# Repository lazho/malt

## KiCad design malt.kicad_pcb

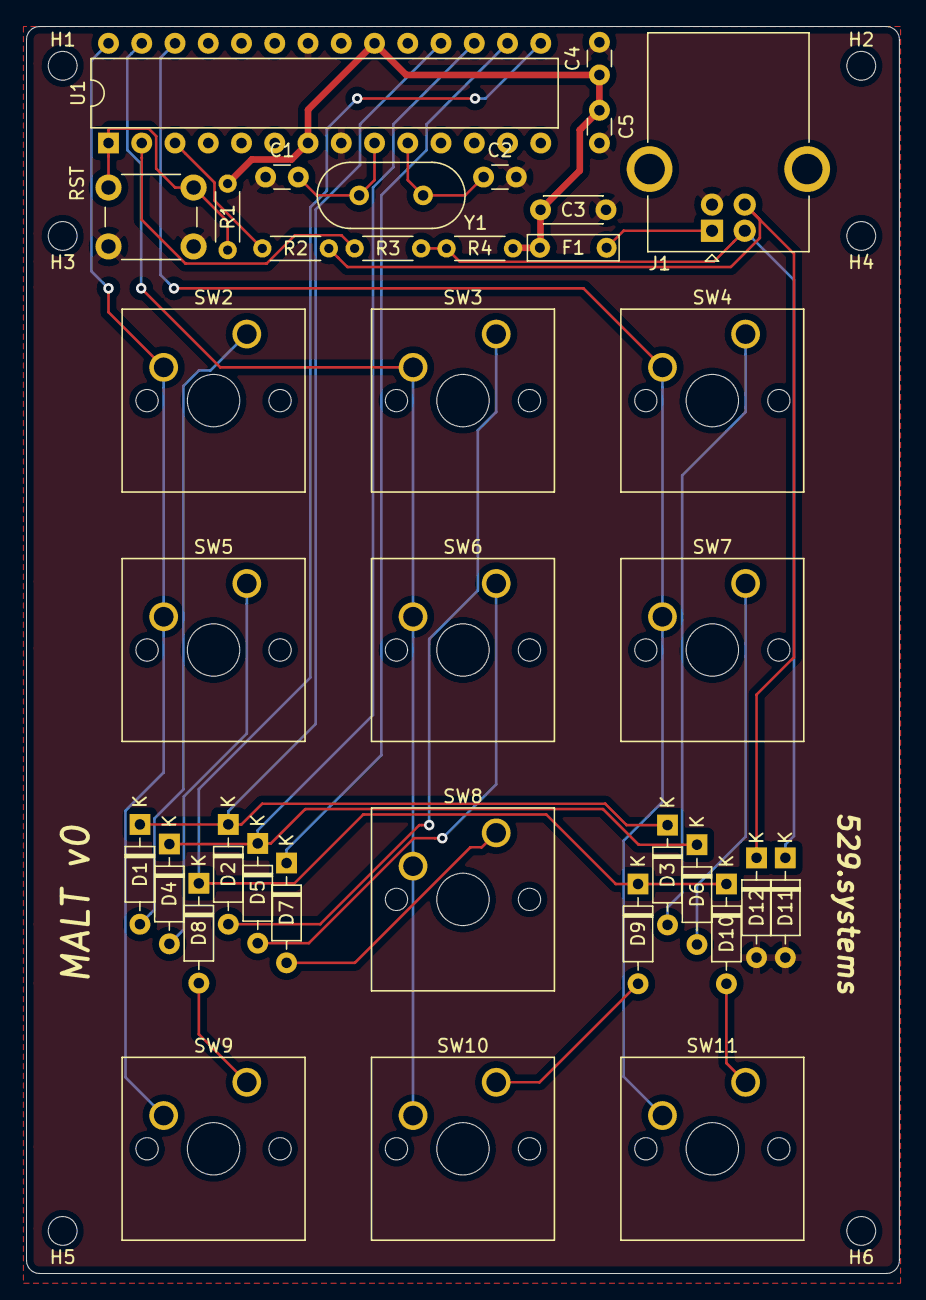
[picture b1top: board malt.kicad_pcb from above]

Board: 2 copper layers, 66.7 x 95.2 mm, 42 parts (0 on the bottom side), 27 nets.

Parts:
C1, C2: 20p; C_Disc_D3.0mm_W1.6mm_P2.50mm
C3: 4.7u; C_Disc_D4.3mm_W1.9mm_P5.00mm
C4, C5: 0.1u; C_Disc_D3.0mm_W1.6mm_P2.50mm
D1, D2, D3, D4, D5, D6, D7, D8, D9, D10: 1N4148; D_DO-35_SOD27_P7.62mm_Horizontal
D11, D12: 3.6V; D_DO-35_SOD27_P7.62mm_Horizontal
F1: Polyfuse_Small; Polyfuse_5.1mm
H1: M1; MountingHole_2.2mm_M2
H2: M2; MountingHole_2.2mm_M2
H3: M3; MountingHole_2.2mm_M2
H4: M4; MountingHole_2.2mm_M2
H5: M5; MountingHole_2.2mm_M2
H6: M6; MountingHole_2.2mm_M2
J1: USB_B; USB_B_OST_USB-B1HSxx_Horizontal
R1: 10k; R_Axial_DIN0204_L3.6mm_D1.6mm_P5.08mm_Horizontal
R2, R3: 75; R_Axial_DIN0204_L3.6mm_D1.6mm_P5.08mm_Horizontal
R4: 1.5k; R_Axial_DIN0204_L3.6mm_D1.6mm_P5.08mm_Horizontal
RST: RESET; SW_PUSH_6mm
SW2: NAV1; SW_Cherry_MX_1.00u_PCB_Aligned
SW3: NAV2; SW_Cherry_MX_1.00u_PCB_Aligned
SW4: NAV3; SW_Cherry_MX_1.00u_PCB_Aligned
SW5: NAV4; SW_Cherry_MX_1.00u_PCB_Aligned
SW6: NAV5; SW_Cherry_MX_1.00u_PCB_Aligned
SW7: NAV6; SW_Cherry_MX_1.00u_PCB_Aligned
SW8: UP; SW_Cherry_MX_1.00u_PCB_Aligned
SW9: LEFT; SW_Cherry_MX_1.00u_PCB_Aligned
SW10: DOWN; SW_Cherry_MX_1.00u_PCB_Aligned
SW11: RIGHT; SW_Cherry_MX_1.00u_PCB_Aligned
U1: ATmega328P-PU; DIP-28_W7.62mm
Y1: 16MHz; Crystal_HC49-U_Vertical

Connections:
+5V: C3.1, C4.1, C5.1, F1.1, R1.1, R4.1, U1.7, U1.20
COL1: SW2.2, SW5.2, SW9.2, U1.28
COL2: SW3.2, SW6.2, SW8.2, SW10.2, U1.27
COL3: SW4.2, SW7.2, SW11.2, U1.26
GND: C1.1, C2.2, C3.2, C4.2, C5.2, D11.2, D12.2, J1.4, RST.2, U1.8, U1.22
unnamed: D1.2, SW2.1
unnamed: D2.2, SW3.1
unnamed: D3.2, SW4.1
unnamed: D4.2, SW5.1
unnamed: D5.2, SW6.1
unnamed: D6.2, SW7.1
unnamed: D7.2, SW8.1
unnamed: D8.2, SW9.1
unnamed: D9.2, SW10.1
unnamed: D10.2, SW11.1
unnamed: D11.1, J1.2, R3.2, R4.2
unnamed: D12.1, J1.3, R2.2
unnamed: F1.2, J1.1
RESET: R1.2, RST.1, U1.1
ROW1: D1.1, D2.1, D3.1, U1.18
ROW2: D4.1, D5.1, D6.1, U1.17
ROW3: D7.1, U1.16
ROW4: D8.1, D9.1, D10.1, U1.15
USB_D+: R2.1, U1.3
USB_D-: R3.1, U1.2
XTAL1: C1.2, U1.9, Y1.1
XTAL2: C2.1, U1.10, Y1.2

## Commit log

2019-08-03 fix gitignore and readme
2019-08-03 initial design
